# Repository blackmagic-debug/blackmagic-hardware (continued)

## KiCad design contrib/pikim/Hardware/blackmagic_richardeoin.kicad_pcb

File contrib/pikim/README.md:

Black Magic Pikim Clone
========================================

Pikim is a version of the Black Magic Mini board.

It is an easy-to-use board used for debugging embedded microcontrollers. It supports several targets from manufacturers such as STMicroelectronics, Atmel, Nordic Semiconductor, NXP, Texas Instruments, Freescale, Silicon Labs, Xilinx or Raspberry Pi.

GNU debugger
-------------------
The Black Magic GNU DeBugger (GDB) server features:
* Automatic target detection
* No need for target specific configuration scripts
* Easily scriptable
* Interface to the host computer does not require special drivers
* Full debugging functionality
* Works with Windows, Linux and Mac environments

Repository Contents
-------------------

* **/Production** - Gerber files, drill files, BOM, CPL file
* **/Hardware** - KiCad PCB files, footprints library
* **/Documents** - Schematics pdf

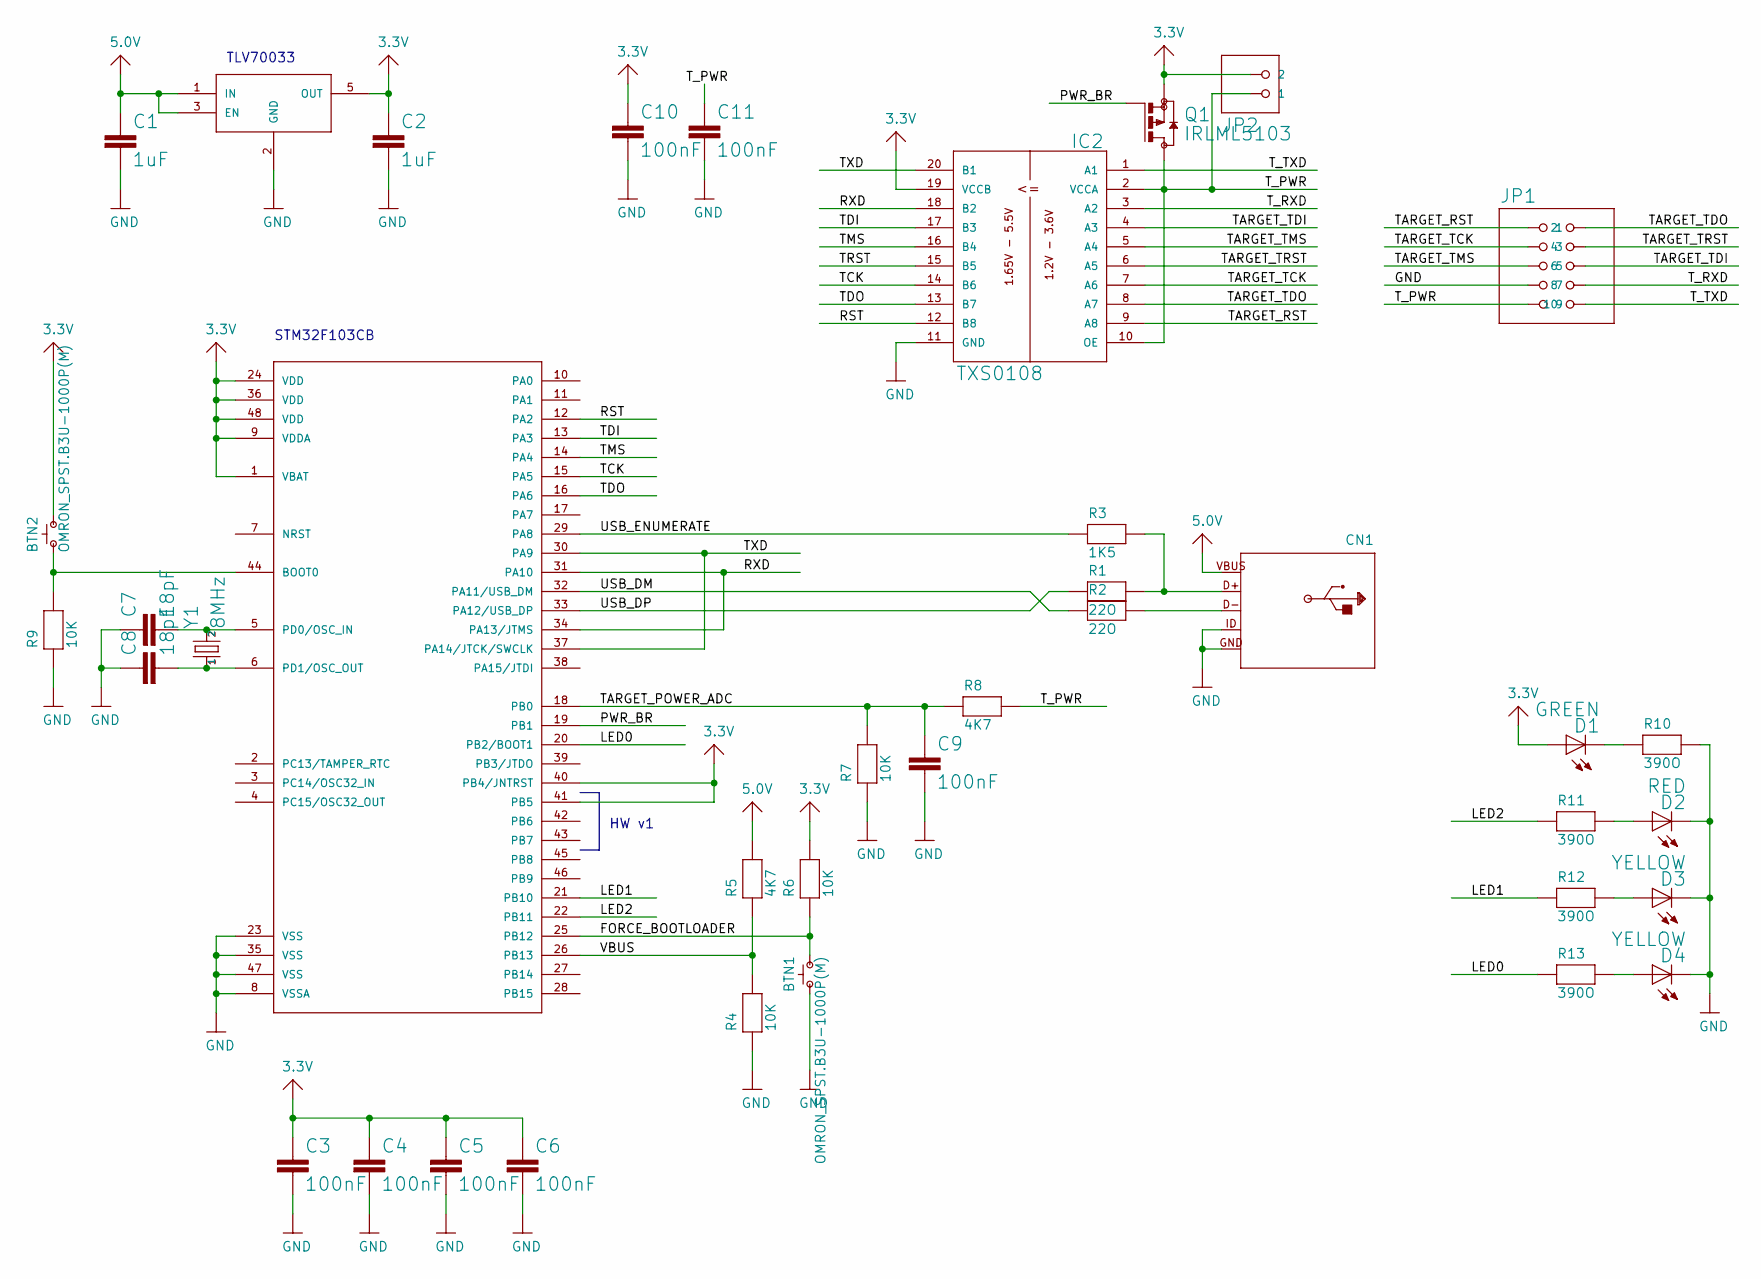
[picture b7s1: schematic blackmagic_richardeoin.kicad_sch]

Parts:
BTN1, BTN2: OMRON_SPST.B3U-1000P(M); BLACKMAGIC_RICHARDEOIN_OMRON_B3U-1000P(M); LCSC Number Part C231329
C1, C2: 1uF; RESISTOR_C0603K; LCSC Number Part C1592
C3, C4, C5, C6, C9, C10, C11: 100nF; RESISTOR_C0603K; LCSC Number Part C1591
C7, C8: 18pF; RESISTOR_C0603K; LCSC Number Part C1647
CN1: MICROBUILDER_V3_USB-MINIB; LCSC Number Part C136452
D1: GREEN; LED_CHIPLED_0603; LCSC Number Part C434420
D2: RED; LED_CHIPLED_0603; LCSC Number Part C375444
D3, D4: YELLOW; LED_CHIPLED_0603; LCSC Number Part C89811
IC1: STM32F_48PIN; STM32F_TQFP48; LCSC Number Part C8304
IC2: TXS0108; DAN-TRANSLATE_TSSOP20; LCSC Number Part C17206
IC3: TLV70033DCK; BLACKMAGIC_RICHARDEOIN_TLV700_SC70-5L; LCSC Number Part C47945
JP1: PINHEAD_2X05
JP2: PINHEAD-2_1X02SMD_90-BIGPADS
Q1: IRLML5103; TRANSISTOR-SMALL-SIGNAL_SOT23; LCSC Number Part C2591
R1, R2: 22O; MICROBUILDER_0603-MINI; LCSC Number Part C23345
R3: 1K5; MICROBUILDER_0603-MINI; LCSC Number Part C22843
R4, R6, R7, R9: 10K; MICROBUILDER_0603-MINI; LCSC Number Part C25804
R5, R8: 4K7; MICROBUILDER_0603-MINI; LCSC Number Part C23162
R10, R11, R12, R13: 390O; MICROBUILDER_0603-MINI; LCSC Number Part C23151
Y1: 8MHz; SPARKFUN_CRYSTAL-SMD-5X3; LCSC Number Part C431529

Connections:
3.3V: BTN2.2, C2.1, C3.1, C4.1, C5.1, C6.1, C10.1, D1.A, IC1.1 (VBAT), IC1.9 (VDDA), IC1.24 (VDD), IC1.36 (VDD), IC1.40 (PB4/JNTRST), IC1.41 (PB5), IC1.48 (VDD), IC2.19 (VCCB), IC3.5 (OUT), JP2.2, Q1.2 (S), R6.2
5.0V: C1.1, CN1.VBUS, IC3.1 (IN), IC3.3 (EN), R5.2
BOOT0: BTN2.1, IC1.44 (BOOT0), R9.2
D+: CN1.D+, R1.2, R3.2
D-: CN1.D-, R2.2
FORCE_BOOTLOADER: BTN1.1, IC1.25 (PB12), R6.1
GND: BTN1.2, C1.2, C2.2, C3.2, C4.2, C5.2, C6.2, C7.1, C8.1, C9.2, C10.2, C11.2, CN1.GND, CN1.GND1, CN1.GND2, CN1.GND3, CN1.GND4, CN1.ID, D2.C, D3.C, D4.C, IC1.8 (VSSA), IC1.23 (VSS), IC1.35 (VSS), IC1.47 (VSS), IC2.11 (GND), IC3.2 (GND), JP1.7, R4.1, R7.1, R9.1, R10.2
LED0: IC1.20 (PB2/BOOT1), R13.1
LED1: IC1.21 (PB10), R12.1
LED2: IC1.22 (PB11), R11.1
LPC_XTAL2: C8.2, IC1.6 (PD1/OSC_OUT), Y1.1
unnamed: D2.A, R11.2
unnamed: D1.C, R10.1
unnamed: D3.A, R12.2
unnamed: D4.A, R13.2
OSC_IN: C7.2, IC1.5 (PD0/OSC_IN), Y1.3 (2)
PWR_BR: IC1.19 (PB1), Q1.1 (G)
RST: IC1.12 (PA2), IC2.12 (B8)
RXD: IC1.31 (PA10), IC1.34 (PA13/JTMS), IC2.18 (B2)
TARGET_POWER_ADC: C9.1, IC1.18 (PB0), R7.2, R8.1
TARGET_RST: IC2.9 (A8), JP1.1
TARGET_TCK: IC2.7 (A6), JP1.3
TARGET_TDI: IC2.4 (A3), JP1.6
TARGET_TDO: IC2.8 (A7), JP1.2
TARGET_TMS: IC2.5 (A4), JP1.5
TARGET_TRST: IC2.6 (A5), JP1.4
TCK: IC1.15 (PA5), IC2.14 (B6)
TDI: IC1.13 (PA3), IC2.17 (B3)
TDO: IC1.16 (PA6), IC2.13 (B7)
TMS: IC1.14 (PA4), IC2.16 (B4)
TRST: IC2.15 (B5)
TXD: IC1.30 (PA9), IC1.37 (PA14/JTCK/SWCLK), IC2.20 (B1)
T_PWR: C11.1, IC2.2 (VCCA), IC2.10 (OE), JP1.9, JP2.1, Q1.3 (D), R8.2
T_RXD: IC2.3 (A2), JP1.8
T_TXD: IC2.1 (A1), JP1.10
USB_DM: IC1.32 (PA11/USB_DM), R2.1
USB_DP: IC1.33 (PA12/USB_DP), R1.1
USB_ENUMERATE: IC1.29 (PA8), R3.1
VBUS: IC1.26 (PB13), R4.2, R5.1

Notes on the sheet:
STM32F103CB
HW v1
TLV70033

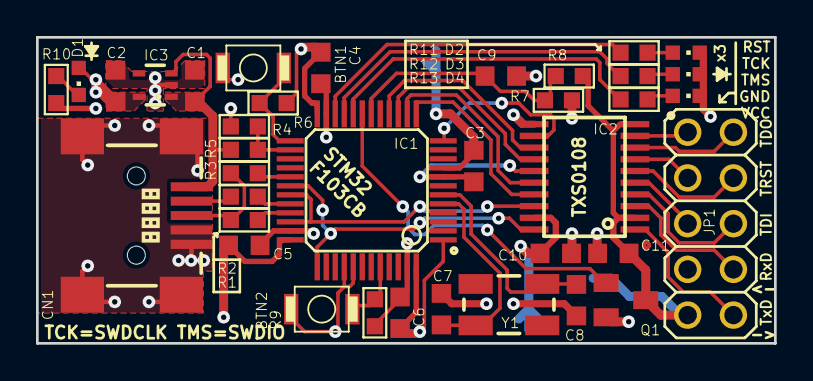
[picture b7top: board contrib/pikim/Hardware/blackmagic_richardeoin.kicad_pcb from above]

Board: 2 copper layers, 41.0 x 17.0 mm, 39 parts (1 on the bottom side), 38 nets.

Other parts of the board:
U$32: LP_NUMBER_SILK_TOP

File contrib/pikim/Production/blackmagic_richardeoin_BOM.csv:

"Source:","C:\Users\Sergio\Documents\EOS\pikim\blackmagic_richardeoin.kicad_sch"
"Date:","08/09/2022 11:47:48"
"Tool:","Eeschema (6.0.7)"
"Generator:","C:\Program Files\KiCad\6.0\bin\scripting\plugins/bom_csv_grouped_by_value.py"
"Component Count:","36"

"Individual Components:"

"Item","Qty","Reference(s)","Value","LibPart","Footprint","Datasheet","Feld5","Feld6","LCSC Number Part"
"","","BTN1","OMRON_SPST.B3U-1000P(M)","blackmagic_richardeoin-rescue:BLACKMAGIC_RICHARDEOIN_OMRON_SPST.B3U-1000P_M_","BLACKMAGIC_RICHARDEOIN_OMRON_B3U-1000P(M)","","","","C231329"
"","","BTN2","OMRON_SPST.B3U-1000P(M)","blackmagic_richardeoin-rescue:BLACKMAGIC_RICHARDEOIN_OMRON_SPST.B3U-1000P_M_","BLACKMAGIC_RICHARDEOIN_OMRON_B3U-1000P(M)","","","","C231329"
"","","C1","1uF","blackmagic_richardeoin-rescue:RESISTOR_C-EUC0603K","RESISTOR_C0603K","","","","C1592"
"","","C2","1uF","blackmagic_richardeoin-rescue:RESISTOR_C-EUC0603K","RESISTOR_C0603K","","","","C1592"
"","","C3","100nF","blackmagic_richardeoin-rescue:RESISTOR_C-EUC0603K","RESISTOR_C0603K","","","","C1591"
"","","C4","100nF","blackmagic_richardeoin-rescue:RESISTOR_C-EUC0603K","RESISTOR_C0603K","","","","C1591"
"","","C5","100nF","blackmagic_richardeoin-rescue:RESISTOR_C-EUC0603K","RESISTOR_C0603K","","","","C1591"
"","","C6","100nF","blackmagic_richardeoin-rescue:RESISTOR_C-EUC0603K","RESISTOR_C0603K","","","","C1591"
"","","C7","18pF","blackmagic_richardeoin-rescue:RESISTOR_C-EUC0603K","RESISTOR_C0603K","","","","C1647"
"","","C8","18pF","blackmagic_richardeoin-rescue:RESISTOR_C-EUC0603K","RESISTOR_C0603K","","","","C1647"
"","","C9","100nF","blackmagic_richardeoin-rescue:RESISTOR_C-EUC0603K","RESISTOR_C0603K","","","","C1591"
"","","C10","100nF","blackmagic_richardeoin-rescue:RESISTOR_C-EUC0603K","RESISTOR_C0603K","","","","C1591"
"","","C11","100nF","blackmagic_richardeoin-rescue:RESISTOR_C-EUC0603K","RESISTOR_C0603K","","","","C1591"
"","","CN1","~","blackmagic_richardeoin-rescue:MICROBUILDER_V3_USBMINIB","MICROBUILDER_V3_USB-MINIB","","","","C136452"
"","","D1","GREEN","blackmagic_richardeoin-rescue:LED_LEDCHIPLED_0603","LED_CHIPLED_0603","","","","C434420"
"","","D2","RED","blackmagic_richardeoin-rescue:LED_LEDCHIPLED_0603","LED_CHIPLED_0603","","","","C375444"
"","","D3","YELLOW","blackmagic_richardeoin-rescue:LED_LEDCHIPLED_0603","LED_CHIPLED_0603","","","","C89811"
"","","D4","YELLOW","blackmagic_richardeoin-rescue:LED_LEDCHIPLED_0603","LED_CHIPLED_0603","","","","C89811"
"","","IC1","STM32F_48PIN","blackmagic_richardeoin-rescue:STM32F_STM32F_48PIN","STM32F_TQFP48","","","","C8304"
"","","IC2","TXS0108","blackmagic_richardeoin-rescue:DAN-TRANSLATE_TX0108PWR","DAN-TRANSLATE_TSSOP20","","","","C17206"
"","","IC3","TLV70033DCK","blackmagic_richardeoin-rescue:BLACKMAGIC_RICHARDEOIN_TLV700_TLV700DCK","BLACKMAGIC_RICHARDEOIN_TLV700_SC70-5L","","","","C47945"
"","","Q1","IRLML5103","blackmagic_richardeoin-rescue:TRANSISTOR-SMALL-SIGNAL_BSS84","TRANSISTOR-SMALL-SIGNAL_SOT23","","","","C2591"
"","","R1","22O","blackmagic_richardeoin-rescue:MICROBUILDER_RESISTOR0603MINI","MICROBUILDER_0603-MINI","","","","C23345"
"","","R2","22O","blackmagic_richardeoin-rescue:MICROBUILDER_RESISTOR0603MINI","MICROBUILDER_0603-MINI","","","","C23345"
"","","R3","1K5","blackmagic_richardeoin-rescue:MICROBUILDER_RESISTOR0603MINI","MICROBUILDER_0603-MINI","","","","C22843"
"","","R4","10K","blackmagic_richardeoin-rescue:MICROBUILDER_RESISTOR0603MINI","MICROBUILDER_0603-MINI","","","","C25804"
"","","R5","4K7","blackmagic_richardeoin-rescue:MICROBUILDER_RESISTOR0603MINI","MICROBUILDER_0603-MINI","","","","C23162"
"","","R6","10K","blackmagic_richardeoin-rescue:MICROBUILDER_RESISTOR0603MINI","MICROBUILDER_0603-MINI","","","","C25804"
"","","R7","10K","blackmagic_richardeoin-rescue:MICROBUILDER_RESISTOR0603MINI","MICROBUILDER_0603-MINI","","","","C25804"
"","","R8","4K7","blackmagic_richardeoin-rescue:MICROBUILDER_RESISTOR0603MINI","MICROBUILDER_0603-MINI","","","","C23162"
"","","R9","10K","blackmagic_richardeoin-rescue:MICROBUILDER_RESISTOR0603MINI","MICROBUILDER_0603-MINI","","","","C25804"
"","","R10","390O","blackmagic_richardeoin-rescue:MICROBUILDER_RESISTOR0603MINI","MICROBUILDER_0603-MINI","","","","C23151"
"","","R11","390O","blackmagic_richardeoin-rescue:MICROBUILDER_RESISTOR0603MINI","MICROBUILDER_0603-MINI","","","","C23151"
"","","R12","390O","blackmagic_richardeoin-rescue:MICROBUILDER_RESISTOR0603MINI","MICROBUILDER_0603-MINI","","","","C23151"
"","","R13","390O","blackmagic_richardeoin-rescue:MICROBUILDER_RESISTOR0603MINI","MICROBUILDER_0603-MINI","","","","C23151"
"","","Y1","8MHz","blackmagic_richardeoin-rescue:SPARKFUN_CRYSTAL5X3","SPARKFUN_CRYSTAL-SMD-5X3","","1","2","C431529"

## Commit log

2011-02-06 Added Black Magic Probe schematic.
2011-02-06 Fixed schematic to match old netlist.
2011-02-06 Added PCB layout.
2011-02-06 Added copyright notice to pcb layout.
2011-02-06 Named PCB layout.
2011-02-08 Added some missing values and footprints to schematic.
2012-03-25 Added new mini hardware design.
2012-04-02 hardware: Removed solder paste openings on fiducials.
2012-04-12 Added a Makefile for generation of some hardware outputs.
2013-03-16 Add a version of BMP-mini optimized for manual production
    This commit adds a variant of the Blackmagic Mini that uses only 0603
    parts and standard connectors for better availability and easier manual
    soldering.
    Additionally, another voltage regulator has been used that is
    cheaper, pin-compatible and has better characteristics.
2013-03-16 Moved entropia design to contrib directory and added description.
2013-03-17 Modified BMP Mini with extra connectors
2013-06-18 hardware: Correct micro part number to STM32F103CB.
2013-08-18 Added new contrib hardware folder including README
2013-08-18 Added blank parts list
2013-08-18 Majority of Components in place
2013-08-18 Major components added to parts list
2013-08-18 Added LEDs
2013-08-18 Attempt to fix table
2013-08-19 Schematic provisionally complete
2013-08-19 Completed board layout
2013-08-19 Completed parts list
2013-08-19 Fixed final list of parts list
2013-08-19 Added links to parts list
2013-08-19 Changed text on the end of the board to "ARM Cortex Debug"
2013-08-19 Added switch on BOOT0
2013-08-19 Wrote README text
2013-08-19 Fixed up README
2013-08-19 Added image to README
2013-08-19 Fixed image in README
2013-08-19 Removed mouse cursor from board image!
2013-08-19 Fixed relative link in README
2013-08-19 Added pdf of schematic
2013-08-19 Spelling error!
2013-08-19 Fixed line endings in README
2013-09-04 Renamed schematic PDF
2013-09-04 Made all the board layers visible
2013-09-04 Added assembly photos
2013-09-04 Added more description about the BOOT0 pin
2013-09-04 Added photos
2013-09-04 Fixed Assembly photo
2013-09-04 Added assembly descriptions
2013-09-04 Tided up README, added note about board being proven
2013-09-04 Made assembly notes titles
2019-02-20 Create Ghetto-gospel
2020-07-18 added usb-c version with rx tx signal on jtag connector
2020-07-19 added footprints
2020-07-19 created layout
2020-07-20 changed silkscreen
2020-07-20 added hardware identification option and TDO optional UART connection
2020-07-20 layouted new changes, added keepout for tag connect, improved gnd plane
2020-08-04 updated schematic and layout
2020-08-04 updated schematic and layout, added fabrication data
2022-09-01 Rename contributed hardware design and add info + images.
2022-09-01 Edits for formatting
2022-09-14 Add pikim schematic
2022-09-14 Add pikim KiCad files
2022-09-14 Add pikim CPL file
2022-09-14 Add pikim Gerber files
2022-09-14 Add pikim files
2022-09-14 Add pikim drill files
2022-09-14 Add pikim BOM
2022-09-14 Add pikim README
2022-09-14 Add pikim LICENSE
2022-09-14 Add pikim gitignore
2022-09-14 Add pikim gitattributes
2022-09-14 Add railgun kicad files
2022-09-14 Add railgun schematic
2022-09-14 Add railgun footprints library
2022-09-14 Add railgun images
2022-09-14 Add railgun README
2022-09-14 Add railgun BOM
2022-09-14 Add railgun drill files
2022-09-14 Add railgun Gerber files
2022-09-14 Add railgun CPL file
2022-09-14 Add railgun LICENSE
2022-09-14 Add railgun gitignore
2022-09-14 Add railgun gitattributes
2022-09-14 Add rs-daviid5 gitattributes
2022-09-14 Add rs-daviid5 gitignore
2022-09-14 Add rs-daviid5 schematic
2022-09-14 Add rs-daviid5 kicad files
2022-09-14 Add rs-daviid5 footprints library
2022-09-14 Add rs-daviid5 LICENSE
2022-09-14 Add rs-daviid5 CPL file
2022-09-14 Add rs-daviid5 Gerber files
2022-09-14 Add rs-daviid5 drill files
2022-09-14 Add rs-daviid5 BOM
2022-09-14 Add rs-daviid5 README
2022-09-14 Add rs-daviid5 images
2022-09-14 Add entropia gitattributes
2022-09-14 Add entropia gitignore
2022-09-14 Move entropia Eagle files
2022-09-14 Add entropia schematic
2022-09-14 Add entropia kicad files
2022-09-14 Add entropia LICENSE
2022-09-14 Add entropia CPL file
2022-09-14 Add entropia footprints library
2022-09-14 Add entropia images
2022-09-14 Move entropia Eagle README
2022-09-14 Add entropia README
2022-09-14 Add entropia BOM
2022-09-14 Add entropia drill files
2022-09-14 Add entropia Gerber files
2022-09-14 Move entropia footprints library
2022-09-14 Move entropia KiCad files
2022-09-14 Add richardeoin gitattributes
2022-09-14 Add richardeoin gitignore
2022-09-14 Move richardeoin Eagle files
2022-09-14 Add richardeoin schematic
2022-09-14 Add richardeoin kicad files
2022-09-14 Add richardeoin LICENSE
2022-09-14 Add richardeoin footprints library
2022-09-14 Add richardeoin CPL file
2022-09-14 Add richardeoin README
2022-09-14 Add richardeoin images
2022-09-14 Add richardeoin BOM
2022-09-14 Add richardeoin drill files
2022-09-14 Add richardeoin Gerber files
2022-09-14 Add emeb gitattributes
2022-09-14 Add emeb gitignore
2022-09-14 Move emeb gEDA files
2022-09-14 Add emeb schematic
2022-09-14 Add emeb kicad files
2022-09-14 Add emeb footprints library
2022-09-14 Add emeb LICENSE
2022-09-14 Add emeb CPL file
2022-09-14 Add emeb README
2022-09-14 Add emeb images
2022-09-14 Add emeb BOM
2022-09-14 Add emeb drill files
2022-09-14 Add emeb Gerber files
2022-09-14 Add esp8266 gitattributes
2022-09-14 Add esp8266 gitignore
2022-09-14 Add esp8266 schematic
2022-09-14 Add esp8266 kicad files
2022-09-14 Add esp8266 LICENSE
2022-09-14 Add esp8266 images
2022-09-14 Add esp8266 README
2022-09-14 Add esp8266 BOM
2022-09-14 Add esp8266 drill files
2022-09-14 Add esp8266 CPL file
2022-09-14 Add esp8266 Gerber files
2026-02-23 We moved to codeberg. See README
